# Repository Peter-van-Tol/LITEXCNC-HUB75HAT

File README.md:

# HUB75HAT

A PCB that turns the Colorlight 5A-75B into an easy to use CNC controller for cheap.

This project ist based on:
- [cyber-murmel/chubby-hat](https://github.com/cyber-murmel/chubby-hat)
- [3k/chubby75](https://github.com/q3k/chubby75/tree/master/5a-75b])

The [HUB75HAT](src/HUB75HAT) is 5A-75B motherboard host for a Raspberry Pi CPU. The HUB75HAT connects to the RPI’s GPIO interface and uses SPI for FPGA communication. Three 26 pin header connectors with standard parallel port pinouts and 5V tolerant I/O are provided for compatibility with most parallel port interfaced motion control / CNC breakout cards / multi axis step motor drives.

In addition to the parallel expansion ports, the HUB75HAT provides two RS-485 interfaces for I/O communication to other RS-485 applications, such as the Huanyang VFD series. These RS-485 are directly taken from the RPI’s header (UART0/1 and UART5).

The firmware is flashed onto the 5A-75B by using the RPI’s GPIO pins. There is no need for external programmers.

The motherboard can also be used _without_ the RPI, by using the standard ethernet communication of the 5A-75B. In this case one would loose the ability to use the RS-485 interfaces and an external tool will be required to flash new firmware.

## Breakout boards (BOB)
Breakout boards are available for the HUB75HAT. These BOBs are designed to add functionality to the HUB75HAT by
extending the GPIO from the 3 26 pin header connectors with drivers, receivers, opto-couplers, etc. Currently the
following BOBs are available:
- [BOB4AXIS](src/BOB4AXIS): Supports driving of 4 axis with differential output. Has inputs for the ALARM of the stepper
  drivers for each axis. Also has optocouplers for homing switches. The homing switches can be either NPN or PNP (selectable
  per axis). Adding this BOB would be enough to run a small 3 axis CNC machine with 1 slave axis.
- [BOB4ENCODER](src/BOB4ENCODER): Supports up to 4 encoders with index (5V only). Unused inputs can be used for generic
  IO. This board also has two connections for SERIAL boards, to further expand GPIO for your machine.

## Serial boards (SERIAL)
These boards are still under development. Goal is to extend GPIO with SPI expanders.

## Releases
The table below gives for each board the current status and the latest release. 

| board               | latest release                            |
|---------------------|-------------------------------------------|
| HUB75HAT            | [v1.2](src/HUB75HAT/releases/v1.2/)       |
| HC245T_BYPASS       | [v1.0](src/HC245T_BYPASS//releases/v1.0/) |
| BOB4AXIS            | [v1.1](src/BOB4AXIS/releases/v1.1/)       |
| BOB4ENCODER         | [v1.0](src/BOB4ENCODER/releases/v1.0/)    |

In each release folder you'll find a production folder with:
- a .zip-file which can be uploaded to your favorite PCB manufacturer
- a BOM;
- a position file for assembly (only verified for HUB75HAT, the rest is hand-soldered)

## KiCad Version
The following version of KiCad has been used to design the boards:
```
Application: KiCad x64 on x64
Version: 7.0.7, release build
Libraries:
    wxWidgets 3.2.2
    FreeType 2.12.1
    HarfBuzz 6.0.0
    FontConfig 2.14.1
    libcurl/7.88.1-DEV Schannel zlib/1.2.13

Platform: Windows 10 (build 19044), 64-bit edition, 64 bit, Little endian, wxMSW

Build Info:
    Date: Aug 19 2023 13:12:00
    wxWidgets: 3.2.2 (wchar_t,wx containers)
    Boost: 1.81.0
    OCC: 7.7.1
    Curl: 7.88.1-DEV
    ngspice: 40
    Compiler: Visual C++ 1936 without C++ ABI

Build settings:
    KICAD_SPICE=ON
```

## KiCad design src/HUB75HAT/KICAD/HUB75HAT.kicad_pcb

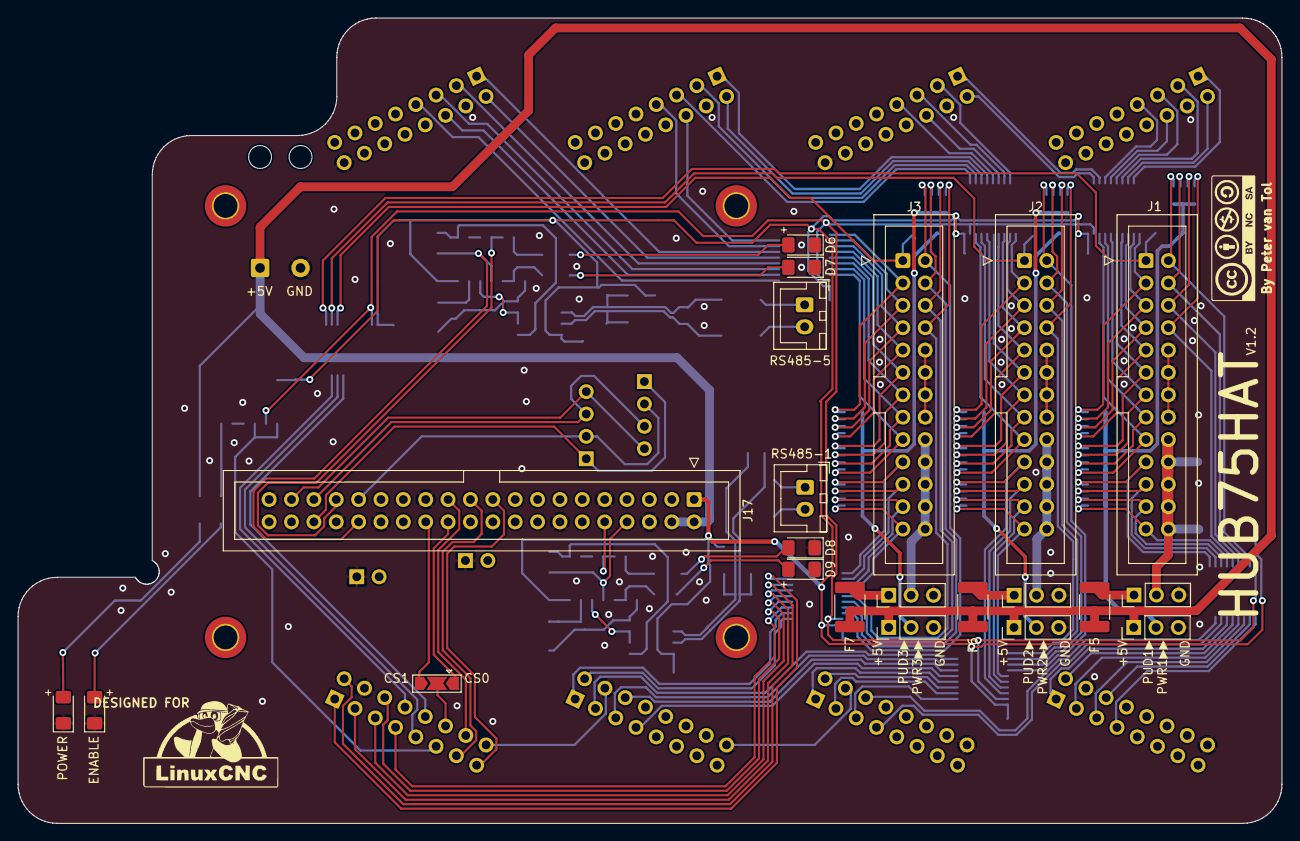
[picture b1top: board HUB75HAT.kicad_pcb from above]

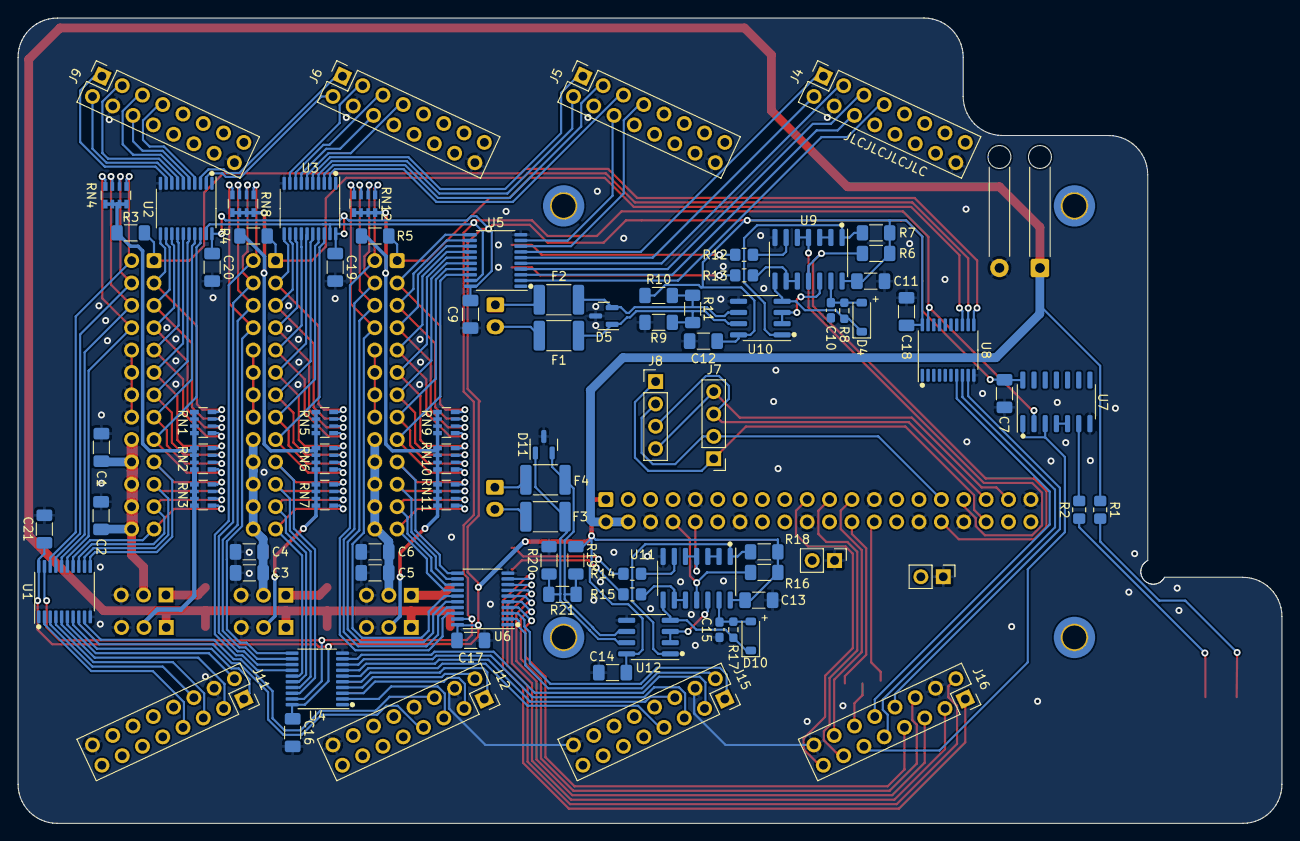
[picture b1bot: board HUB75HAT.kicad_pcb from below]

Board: 2 copper layers, 143.5 x 91.4 mm, 108 parts (86 on the bottom side), 160 nets.

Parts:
C1, C2, C3, C4, C5, C6, C7, C9, C11, C13, C16, C17, C18, C19, C20, C21: 100nF; C_1206_3216Metric_Pad1.33x1.80mm_HandSolder
C10, C15: 33pF; C_0603_1608Metric_Pad1.08x0.95mm_HandSolder
C12, C14: 0.1uF; C_1206_3216Metric_Pad1.33x1.80mm_HandSolder
D1, D2, D6, D7, D8, D9: LED; LED_1206_3216Metric_Pad1.42x1.75mm_HandSolder
D4, D10: 1N4148W; D_SOD-123
D5, D11: SM712_SOT23; SOT-23
F1, F2, F3, F4, F5, F6, F7: 108L; Fuse_1812_4532Metric_Pad1.30x3.40mm_HandSolder
J1, J2, J3: Conn_02x13_Odd_Even; IDC-Header_2x13_P2.54mm_Vertical
J4, J5, J6, J9, J11, J12, J15, J16: HUB75; PinSocket_2x08_P2.54mm_Vertical
J7: v7.0; PinHeader_1x04_P2.54mm_Vertical
J8: v8.0; PinHeader_1x04_P2.54mm_Vertical
J10: Conn_01x02; SolderWire-0.5sqmm_1x02_P4.6mm_D0.9mm_OD2.1mm_Relief
J13: V7.0; PinHeader_1x02_P2.54mm_Vertical
J14: V8.0; PinHeader_1x02_P2.54mm_Vertical
J17: Conn_02x20_Odd_Even; IDC-Header_2x20_P2.54mm_Vertical
JP1, JP2, JP3, JP4, JP5, JP6: Jumper_3_Open; PinHeader_1x03_P2.54mm_Vertical
JP7: SolderJumper_3_Open; SolderJumper-3_P2.0mm_Open_TrianglePad1.0x1.5mm
R1: 300; R_0805_2012Metric_Pad1.20x1.40mm_HandSolder
R2, R12, R13, R14, R15: 150; R_0805_2012Metric_Pad1.20x1.40mm_HandSolder
R3, R4, R5: R; R_1206_3216Metric_Pad1.30x1.75mm_HandSolder
R6, R16: 4.7k; R_1206_3216Metric_Pad1.30x1.75mm_HandSolder
R7, R9, R10, R18, R19, R20: 4.7K; R_1206_3216Metric_Pad1.30x1.75mm_HandSolder
R8, R17: 56k; R_0603_1608Metric_Pad0.98x0.95mm_HandSolder
R11, R21: 120; R_1206_3216Metric_Pad1.30x1.75mm_HandSolder
RN1, RN2, RN3, RN4, RN5, RN6, RN7, RN8, RN9, RN10, RN11, RN12: CN1J4KTTD1002F; R_Array_Convex_4x0603_handsolder
RS485-1, RS485-5: Conn_01x02_Pin; JST_XH_B2B-XH-A_1x02_P2.50mm_Vertical
U1, U2, U3, U4, U5, U6, U8: 74CB3T3245; TSSOP-20_4.4x6.5mm_P0.65mm
U7, U9, U11: 74HC04; SOIC-14_3.9x8.7mm_P1.27mm
U10, U12: MAX3485; SOIC-8_3.9x4.9mm_P1.27mm

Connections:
+3.3V: C7.1, C9.1, C11.1, C12.1, C13.1, C14.1, C16.1, C17.1, C18.1, C19.1, C20.1, C21.1, J17.1, R6.1, R7.1, R10.1, R16.1, R18.1, R19.1, U1.20 (VCC), U2.20 (VCC), U3.20 (VCC), U4.20 (VCC), U5.20 (VCC), U6.20 (VCC), U7.14 (VCC), U8.20 (VCC), U9.14 (VCC), U10.8 (VCC), U11.14 (VCC), U12.8 (VCC)
+5V: F5.1, F6.1, F7.1, J10.1, J17.2, J17.4, JP4.1 (A), JP5.1 (A), JP6.1 (A), R1.1
/JTAG.TCK: J7.1, J8.1, J17.36
/JTAG.TDI: J7.3, J8.3, J17.35
/JTAG.TDO: J7.4, J8.4, J17.37
/JTAG.TMS: J7.2, J8.2, J17.31
ENA: U1.19 (CE), U2.19 (CE), U3.19 (CE), U4.19 (CE), U5.19 (CE), U6.19 (CE), U7.2, U8.19 (CE)
ENA-LED: R2.1, U7.6
ENA_IN: J16.11, U7.1, U7.3
GND: C1.2, C2.2, C3.2, C4.2, C5.2, C6.2, C7.2, C9.2, C10.2, C11.2, C12.2, C13.2, C14.2, C15.2, C16.2, C17.2, C18.2, C19.2, C20.2, C21.2, D1.1 (K), D2.1 (K), D5.3 (common), D6.1 (K), D7.1 (K), D8.1 (K), D9.1 (K), D11.3 (common), J1.10, J1.12, J1.14, J1.16, J2.10, J2.12, J2.14, J2.16, J3.10, J3.12, J3.14, J3.16, J4.4, J4.16, J5.4, J5.16, J6.4, J6.16, J9.4, J9.16, J10.2, J11.4, J11.16, J12.4, J12.16, J13.1, J14.1, J15.4, J15.16, J16.4, J16.16, J17.6, J17.9, J17.14, J17.20, J17.25, J17.30, J17.34, J17.39, JP1.3 (B), JP2.3 (B), JP3.3 (B), JP4.3 (B), JP5.3 (B), JP6.3 (B), R9.2, R20.2, U1.10 (GND), U2.10 (GND), U3.10 (GND), U4.10 (GND), U5.10 (GND), U6.10 (GND), U7.7 (GND), U8.10 (GND), U9.7 (GND), U10.5 (GND), U11.7 (GND), U12.5 (GND)
J1:0: J11.1, U1.7 (A5)
J1:1: J11.2, U1.6 (A4)
J1:2: J11.3, U1.5 (A3)
J1:4: J11.5, U1.4 (A2)
J1:5: J11.6, U1.3 (A1)
J1:6: J11.7, U1.2 (A0)
J2:0: J12.1, U4.5 (A3)
J2:1: J12.2, U4.4 (A2)
J2:2: J12.3, U4.3 (A1)
J2:4: J12.5, U4.2 (A0)
J2:5: J12.6, U1.9 (A7)
J2:6: J12.7, U1.8 (A6)
J3:0: J15.1, U6.3 (A1)
J3:1: J15.2, U6.2 (A0)
J3:2: J15.3, U4.9 (A7)
J3:4: J15.5, U4.8 (A6)
J3:5: J15.6, U4.7 (A5)
J3:6: J15.7, U4.6 (A4)
J4:0: J16.1, U6.9 (A7)
J4:1: J16.2, U6.8 (A6)
J4:2: J16.3, U6.7 (A5)
J4:4: J16.5, U6.6 (A4)
J4:5: J16.6, U6.5 (A3)
J4:6: J16.7, U6.4 (A2)
J4:7: J16.8, U8.9 (A7)
J4:8: J16.9, U8.8 (A6)
J4:9: J16.10, U8.7 (A5)
J5:0: J4.1, U5.7 (A5)
J5:1: J4.2, U5.6 (A4)
J5:2: J4.3, U5.5 (A3)
J5:4: J4.5, U5.4 (A2)
J5:5: J4.6, U5.3 (A1)
J5:6: J4.7, U5.2 (A0)
J6:0: J5.1, U3.5 (A3)
J6:1: J5.2, U3.4 (A2)
J6:2: J5.3, U3.3 (A1)
J6:4: J5.5, U3.2 (A0)
J6:5: J5.6, U5.9 (A7)
J6:6: J5.7, U5.8 (A6)
J7:0: J6.1, U2.3 (A1)
J7:1: J6.2, U2.2 (A0)
J7:2: J6.3, U3.9 (A7)
J7:4: J6.5, U3.8 (A6)
J7:5: J6.6, U3.7 (A5)
J7:6: J6.7, U3.6 (A4)
J8:0: J9.1, U2.9 (A7)
J8:1: J9.2, U2.8 (A6)
J8:2: J9.3, U2.7 (A5)
J8:4: J9.5, U2.6 (A4)
J8:5: J9.6, U2.5 (A3)
J8:6: J9.7, U2.4 (A2)
unnamed: D1.2 (A), R1.2
unnamed: D2.2 (A), R2.2
unnamed: C10.1, D4.2 (A), R8.2, U9.13
unnamed: D4.1 (K), R8.1, U9.8, U10.4 (DI)
unnamed: D5.1 (A1), F1.1, R9.1, R11.1, U10.7 (B)
unnamed: D5.2 (A2), F2.2, R10.2, R11.2, U10.6 (A)
unnamed: D6.2 (A), R12.2
unnamed: D7.2 (A), R13.2
unnamed: D8.2 (A), R14.2
unnamed: D9.2 (A), R15.2
unnamed: C15.1, D10.2 (A), R17.2, U11.13
unnamed: D10.1 (K), R17.1, U11.8, U12.4 (DI)
unnamed: D11.1 (A1), F3.1, R20.1, R21.1, U12.7 (B)
unnamed: D11.2 (A2), F4.2, R19.2, R21.2, U12.6 (A)
unnamed: F2.1, RS485-5.1
unnamed: F1.2, RS485-5.2
unnamed: F4.1, RS485-1.1
unnamed: F3.2, RS485-1.2
unnamed: F5.2, JP1.1 (A)
unnamed: F6.2, JP2.1 (A)
unnamed: F7.2, JP3.1 (A)
unnamed: JP4.2 (C), R3.2, RN1.1 (R1.1), RN1.2 (R2.1), RN1.3 (R3.1), RN1.4 (R4.1), RN2.1 (R1.1), RN2.2 (R2.1), RN2.3 (R3.1), RN2.4 (R4.1), RN3.1 (R1.1), RN3.2 (R2.1), RN3.3 (R3.1), RN3.4 (R4.1), RN4.1 (R1.1), RN4.2 (R2.1), RN4.3 (R3.1), RN4.4 (R4.1)
unnamed: JP5.2 (C), R4.2, RN5.1 (R1.1), RN5.2 (R2.1), RN5.3 (R3.1), RN5.4 (R4.1), RN6.1 (R1.1), RN6.2 (R2.1), RN6.3 (R3.1), RN6.4 (R4.1), RN7.1 (R1.1), RN7.2 (R2.1), RN7.3 (R3.1), RN7.4 (R4.1), RN8.1 (R1.1), RN8.2 (R2.1), RN8.3 (R3.1), RN8.4 (R4.1)
unnamed: JP6.2 (C), R5.2, RN9.1 (R1.1), RN9.2 (R2.1), RN9.3 (R3.1), RN9.4 (R4.1), RN10.1 (R1.1), RN10.2 (R2.1), RN10.3 (R3.1), RN10.4 (R4.1), RN11.1 (R1.1), RN11.2 (R2.1), RN11.3 (R3.1), RN11.4 (R4.1), RN12.1 (R1.1), RN12.2 (R2.1), RN12.3 (R3.1), RN12.4 (R4.1)
unnamed: R12.1, U9.6
unnamed: R13.1, U9.9, U9.10
unnamed: R14.1, U11.6
unnamed: R15.1, U11.9, U11.10
unnamed: U7.4, U7.5
unnamed: U9.2, U9.3
unnamed: U9.12, U10.2 (~RE), U10.3 (DE)
unnamed: R7.2, U9.1, U10.1 (RO)
unnamed: U11.2, U11.3
unnamed: U11.12, U12.2 (~RE), U12.3 (DE)
unnamed: R18.2, U11.1, U12.1 (RO)
PORTA1: J1.1, R3.1, U8.11 (B7)
PORTA2: J1.3, RN1.8 (R1.2), U2.11 (B7)
PORTA3: J1.5, RN1.7 (R2.2), U2.12 (B6)
PORTA4: J1.7, RN1.6 (R3.2), U2.13 (B5)
PORTA5: J1.9, RN1.5 (R4.2), U2.14 (B4)
PORTA6: J1.11, RN2.8 (R1.2), U2.15 (B3)
PORTA7: J1.13, RN2.7 (R2.2), U2.16 (B2)
PORTA8: J1.15, RN2.6 (R3.2), U2.17 (B1)
PORTA9: J1.17, RN2.5 (R4.2), U2.18 (B0)
PORTA10: J1.19, RN3.8 (R1.2), U1.11 (B7)
PORTA11: J1.21, RN3.7 (R2.2), U1.12 (B6)
PORTA12: J1.23, RN3.6 (R3.2), U1.13 (B5)
PORTA13: J1.25, RN3.5 (R4.2), U1.14 (B4)
PORTA14: J1.2, RN4.5 (R4.2), U1.18 (B0)
PORTA15: J1.4, RN4.6 (R3.2), U1.17 (B1)
PORTA16: J1.6, RN4.7 (R2.2), U1.16 (B2)
PORTA17: J1.8, RN4.8 (R1.2), U1.15 (B3)
PORTB1: J2.1, R4.1, U8.12 (B6)
PORTB2: J2.3, RN5.8 (R1.2), U3.11 (B7)
PORTB3: J2.5, RN5.7 (R2.2), U3.12 (B6)
PORTB4: J2.7, RN5.6 (R3.2), U3.13 (B5)
PORTB5: J2.9, RN5.5 (R4.2), U3.14 (B4)
PORTB6: J2.11, RN6.8 (R1.2), U3.15 (B3)
PORTB7: J2.13, RN6.7 (R2.2), U3.16 (B2)
PORTB8: J2.15, RN6.6 (R3.2), U3.17 (B1)
PORTB9: J2.17, RN6.5 (R4.2), U3.18 (B0)
PORTB10: J2.19, RN7.8 (R1.2), U4.18 (B0)
PORTB11: J2.21, RN7.7 (R2.2), U4.17 (B1)
PORTB12: J2.23, RN7.6 (R3.2), U4.16 (B2)
PORTB13: J2.25, RN7.5 (R4.2), U4.15 (B3)
PORTB14: J2.2, RN8.5 (R4.2), U4.14 (B4)
PORTB15: J2.4, RN8.6 (R3.2), U4.13 (B5)
PORTB16: J2.6, RN8.7 (R2.2), U4.12 (B6)
PORTB17: J2.8, RN8.8 (R1.2), U4.11 (B7)
PORTC1: J3.1, R5.1, U8.13 (B5)
PORTC2: J3.3, RN9.8 (R1.2), U5.11 (B7)
PORTC3: J3.5, RN9.7 (R2.2), U5.12 (B6)
PORTC4: J3.7, RN9.6 (R3.2), U5.13 (B5)
PORTC5: J3.9, RN9.5 (R4.2), U5.14 (B4)
PORTC6: J3.11, RN10.8 (R1.2), U5.15 (B3)
PORTC7: J3.13, RN10.7 (R2.2), U5.16 (B2)
PORTC8: J3.15, RN10.6 (R3.2), U5.17 (B1)
PORTC9: J3.17, RN10.5 (R4.2), U5.18 (B0)
PORTC10: J3.19, RN11.8 (R1.2), U6.11 (B7)
PORTC11: J3.21, RN11.7 (R2.2), U6.12 (B6)
PORTC12: J3.23, RN11.6 (R3.2), U6.13 (B5)
PORTC13: J3.25, RN11.5 (R4.2), U6.14 (B4)
PORTC14: J3.2, RN12.5 (R4.2), U6.18 (B0)
PORTC15: J3.4, RN12.6 (R3.2), U6.17 (B1)
PORTC16: J3.6, RN12.7 (R2.2), U6.16 (B2)
PORTC17: J3.8, RN12.8 (R1.2), U6.15 (B3)
POWOPA: C1.1, C2.1, J1.18, J1.20, J1.22, J1.24, J1.26, JP1.2 (C)
POWOPB: C3.1, C4.1, J2.18, J2.20, J2.22, J2.24, J2.26, JP2.2 (C)
POWOPC: C5.1, C6.1, J3.18, J3.20, J3.22, J3.24, J3.26, JP3.2 (C)
RXD1: J17.10, U11.4, U11.5
RXD5: J17.33, U9.4, U9.5
SPI_CE0: J17.24, JP7.1 (A)
SPI_CE1: J17.26, JP7.3 (B)
SPI_CLCK: J16.14, J17.23
SPI_CS: J16.12, JP7.2 (C)
SPI_MISO: J16.13, J17.21
SPI_MOSI: J16.15, J17.19
TXD1: J17.8, R16.2, U11.11
TXD5: J17.32, R6.2, U9.11

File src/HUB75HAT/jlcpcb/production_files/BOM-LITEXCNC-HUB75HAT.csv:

Comment,Designator,Footprint,LCSC
74CB3T3245,"U1,U2,U3,U4,U5,U6,U8",TSSOP-20_4.4x6.5mm_P0.65mm,C15298
33pF,"C10,C15",C_0603_1608Metric_Pad1.08x0.95mm_HandSolder,C1663
150,"R12,R13,R14,R15,R2",R_0805_2012Metric_Pad1.20x1.40mm_HandSolder,C17471
300,R1,R_0805_2012Metric_Pad1.20x1.40mm_HandSolder,C17617
R,"R3,R4,R5",R_1206_3216Metric_Pad1.30x1.75mm_HandSolder,C17902
120,"R11,R21",R_1206_3216Metric_Pad1.30x1.75mm_HandSolder,C17909
4.7K,"R10,R16,R18,R19,R20,R6,R7,R9",R_1206_3216Metric_Pad1.30x1.75mm_HandSolder,C17936
56k,"R17,R8",R_0603_1608Metric_Pad0.98x0.95mm_HandSolder,C23206
100nF,"C1,C11,C12,C13,C14,C16,C17,C18,C19,C2,C20,C21,C3,C4,C5,C6,C7,C9",C_1206_3216Metric_Pad1.33x1.80mm_HandSolder,C24497
SM712_SOT23,"D11,D5",SOT-23,C2687124
CN1J4KTTD1002F,"RN1,RN10,RN11,RN12,RN2,RN3,RN4,RN5,RN6,RN7,RN8,RN9",R_Array_Convex_4x0603_handsolder,C29718
108L,"F1,F2,F3,F4,F5,F6,F7",Fuse_1812_4532Metric_Pad1.30x3.40mm_HandSolder,C782760
MAX3485,"U10,U12",SOIC-8_3.9x4.9mm_P1.27mm,C8963
LED,D1,LED_1206_3216Metric_Pad1.42x1.75mm_HandSolder,
LED,D2,LED_1206_3216Metric_Pad1.42x1.75mm_HandSolder,
74HC04,U9,SOIC-14_3.9x8.7mm_P1.27mm,
74HC04,U11,SOIC-14_3.9x8.7mm_P1.27mm,
1N4148W,D4,D_SOD-123,
1N4148W,D10,D_SOD-123,
LED,D9,LED_1206_3216Metric_Pad1.42x1.75mm_HandSolder,
LED,D6,LED_1206_3216Metric_Pad1.42x1.75mm_HandSolder,
LED,D7,LED_1206_3216Metric_Pad1.42x1.75mm_HandSolder,
LED,D8,LED_1206_3216Metric_Pad1.42x1.75mm_HandSolder,
74HC04,U7,SOIC-14_3.9x8.7mm_P1.27mm,

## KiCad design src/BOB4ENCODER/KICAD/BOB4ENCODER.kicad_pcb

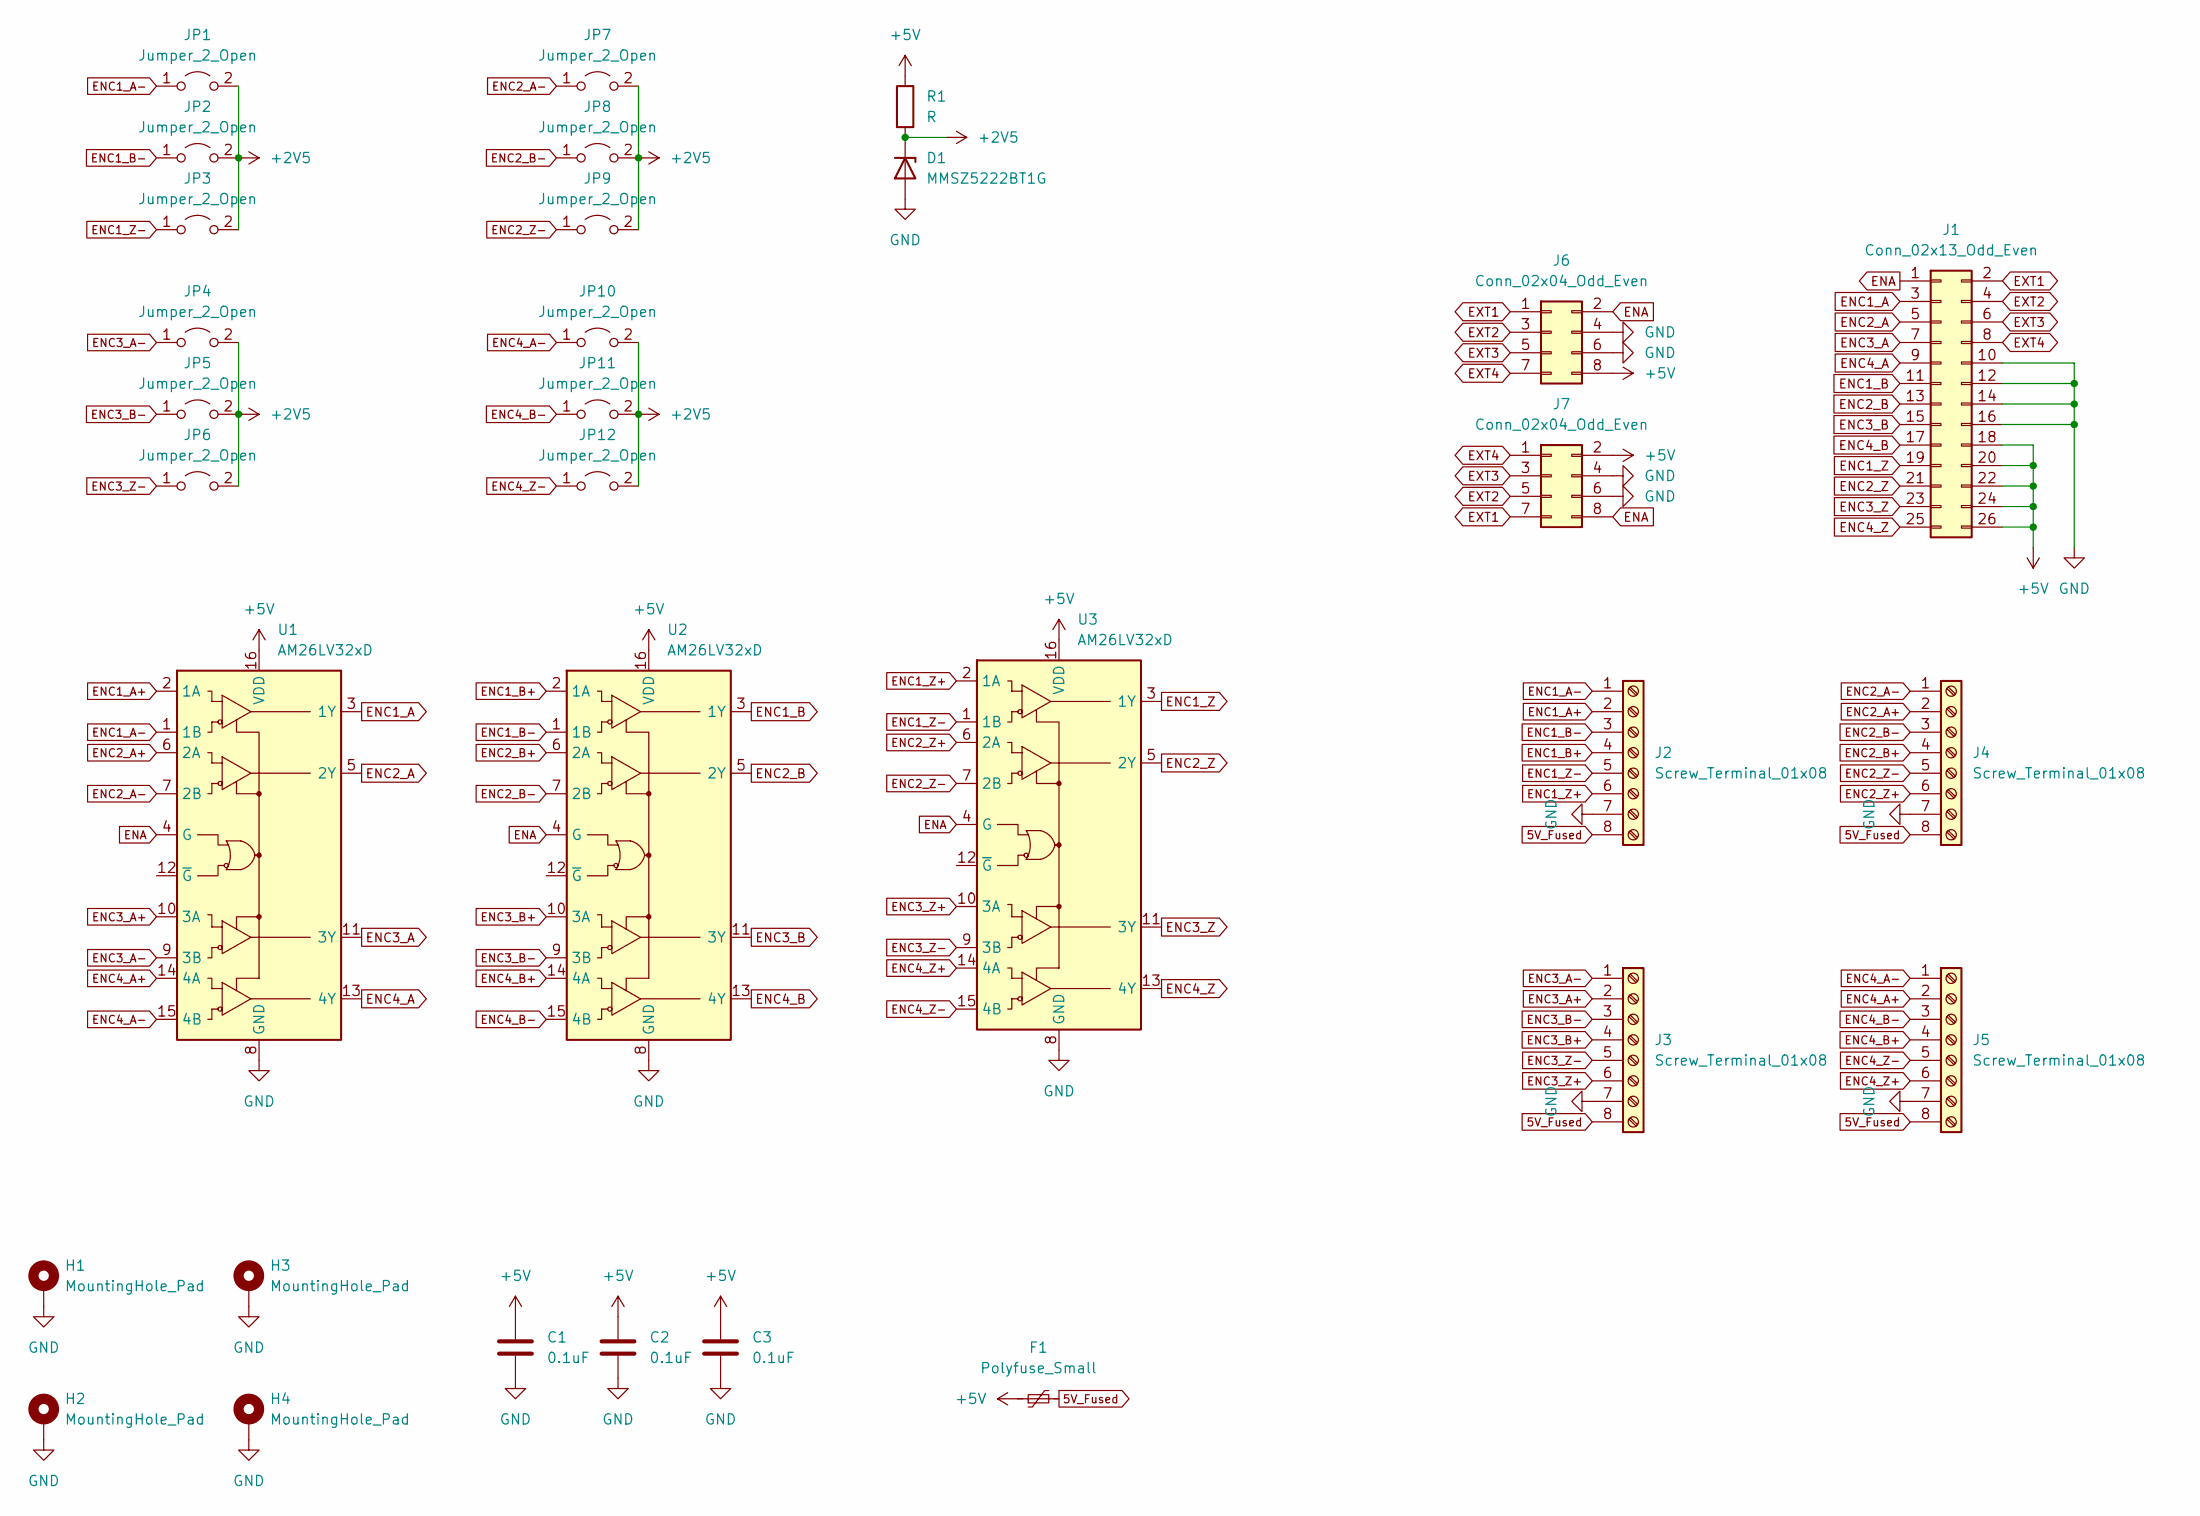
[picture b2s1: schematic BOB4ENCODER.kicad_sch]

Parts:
C1, C2, C3: 0.1uF; C_1206_3216Metric_Pad1.33x1.80mm_HandSolder
D1: MMSZ5222BT1G; D_SOD-123
F1: Polyfuse_Small; R_1812_4532Metric_Pad1.30x3.40mm_HandSolder
H1, H2, H3, H4: MountingHole_Pad; MountingHole_3.2mm_M3_Pad_Via
J1: Conn_02x13_Odd_Even; IDC-Header_2x13_P2.54mm_Vertical
J2, J3, J4, J5: Screw_Terminal_01x08; CONN-TH_8P-P5.08_KF142V-5.08-8P
J6, J7: Conn_02x04_Odd_Even; PinSocket_2x04_P1.27mm_Horizontal
JP1, JP2, JP3, JP4, JP5, JP6, JP7, JP8, JP9, JP10, JP11, JP12: Jumper_2_Open; PinHeader_1x02_P2.54mm_Vertical
R1: R; R_1206_3216Metric_Pad1.30x1.75mm_HandSolder
U1, U2, U3: AM26LV32xD; SOIC-16_3.9x9.9mm_P1.27mm

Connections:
5V_Fused: F1.2, J2.8, J3.8, J4.8, J5.8
+2V5: D1.1 (K), JP1.2 (B), JP2.2 (B), JP3.2 (B), JP4.2 (B), JP5.2 (B), JP6.2 (B), JP7.2 (B), JP8.2 (B), JP9.2 (B), JP10.2 (B), JP11.2 (B), JP12.2 (B), R1.2
+5V: C1.1, C2.1, C3.1, F1.1, J1.18, J1.20, J1.22, J1.24, J1.26, J6.8, J7.2, R1.1, U1.16 (VDD), U2.16 (VDD), U3.16 (VDD)
ENA: J1.1, J6.2, J7.8, U1.4 (G), U2.4 (G), U3.4 (G)
ENC1_A: J1.3, U1.3 (1Y)
ENC1_A+: J2.2, U1.2 (1A)
ENC1_A-: J2.1, JP1.1 (A), U1.1 (1B)
ENC1_B: J1.11, U2.3 (1Y)
ENC1_B+: J2.4, U2.2 (1A)
ENC1_B-: J2.3, JP2.1 (A), U2.1 (1B)
ENC1_Z: J1.19, U3.3 (1Y)
ENC1_Z+: J2.6, U3.2 (1A)
ENC1_Z-: J2.5, JP3.1 (A), U3.1 (1B)
ENC2_A: J1.5, U1.5 (2Y)
ENC2_A+: J4.2, U1.6 (2A)
ENC2_A-: J4.1, JP7.1 (A), U1.7 (2B)
ENC2_B: J1.13, U2.5 (2Y)
ENC2_B+: J4.4, U2.6 (2A)
ENC2_B-: J4.3, JP8.1 (A), U2.7 (2B)
ENC2_Z: J1.21, U3.5 (2Y)
ENC2_Z+: J4.6, U3.6 (2A)
ENC2_Z-: J4.5, JP9.1 (A), U3.7 (2B)
ENC3_A: J1.7, U1.11 (3Y)
ENC3_A+: J3.2, U1.10 (3A)
ENC3_A-: J3.1, JP4.1 (A), U1.9 (3B)
ENC3_B: J1.15, U2.11 (3Y)
ENC3_B+: J3.4, U2.10 (3A)
ENC3_B-: J3.3, JP5.1 (A), U2.9 (3B)
ENC3_Z: J1.23, U3.11 (3Y)
ENC3_Z+: J3.6, U3.10 (3A)
ENC3_Z-: J3.5, JP6.1 (A), U3.9 (3B)
ENC4_A: J1.9, U1.13 (4Y)
ENC4_A+: J5.2, U1.14 (4A)
ENC4_A-: J5.1, JP10.1 (A), U1.15 (4B)
ENC4_B: J1.17, U2.13 (4Y)
ENC4_B+: J5.4, U2.14 (4A)
ENC4_B-: J5.3, JP11.1 (A), U2.15 (4B)
ENC4_Z: J1.25, U3.13 (4Y)
ENC4_Z+: J5.6, U3.14 (4A)
ENC4_Z-: J5.5, JP12.1 (A), U3.15 (4B)
EXT1: J1.2, J6.1, J7.7
EXT2: J1.4, J6.3, J7.5
EXT3: J1.6, J6.5, J7.3
EXT4: J1.8, J6.7, J7.1
GND: C1.2, C2.2, C3.2, D1.2 (A), H1.1, H2.1, H3.1, H4.1, J1.10, J1.12, J1.14, J1.16, J2.7, J3.7, J4.7, J5.7, J6.4, J6.6, J7.4, J7.6, U1.8 (GND), U2.8 (GND), U3.8 (GND)

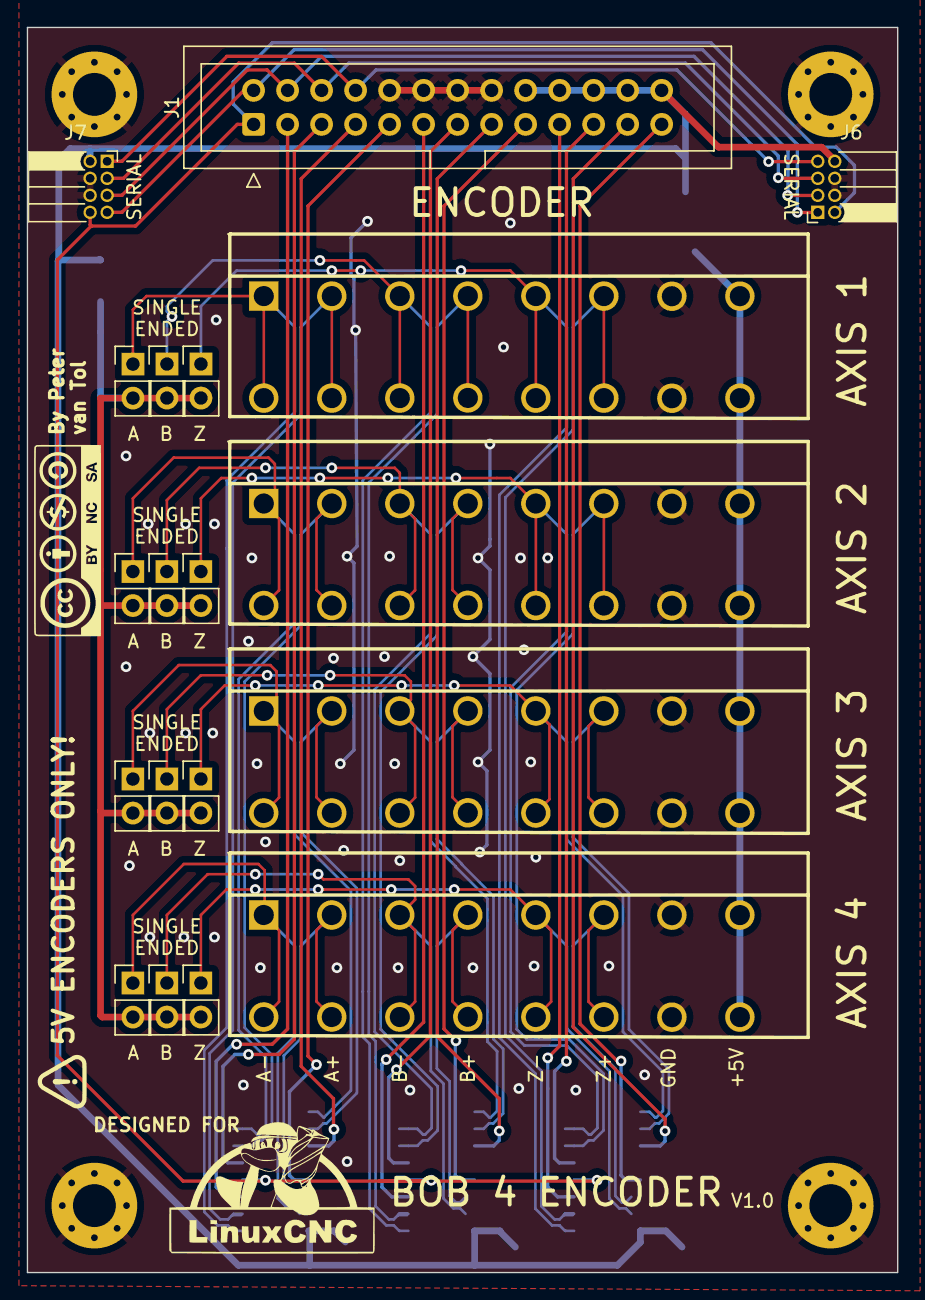
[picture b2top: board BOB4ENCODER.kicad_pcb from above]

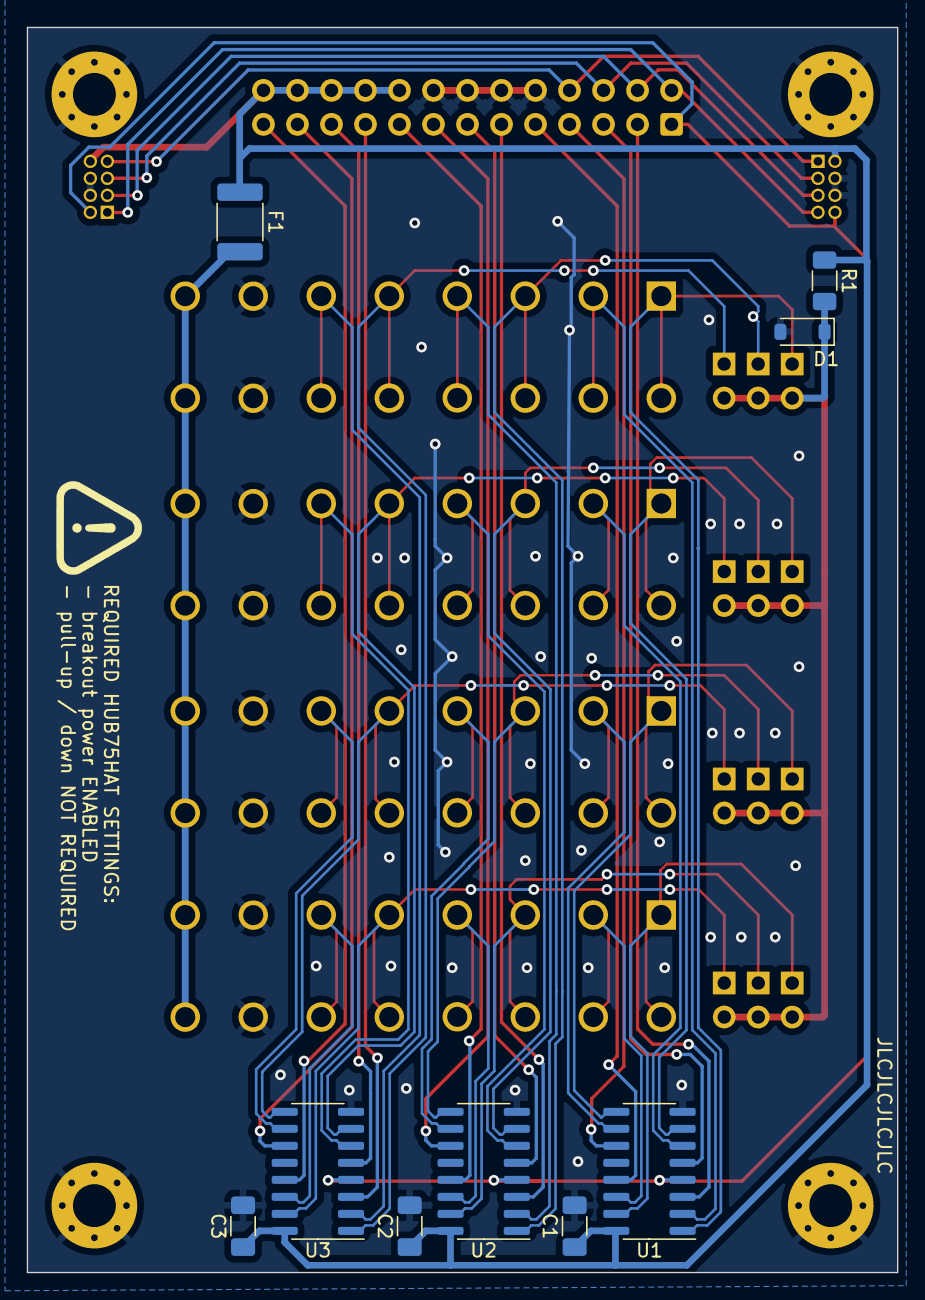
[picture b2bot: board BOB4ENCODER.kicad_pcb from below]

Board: 2 copper layers, 65.0 x 93.0 mm, 32 parts (9 on the bottom side), 45 nets.

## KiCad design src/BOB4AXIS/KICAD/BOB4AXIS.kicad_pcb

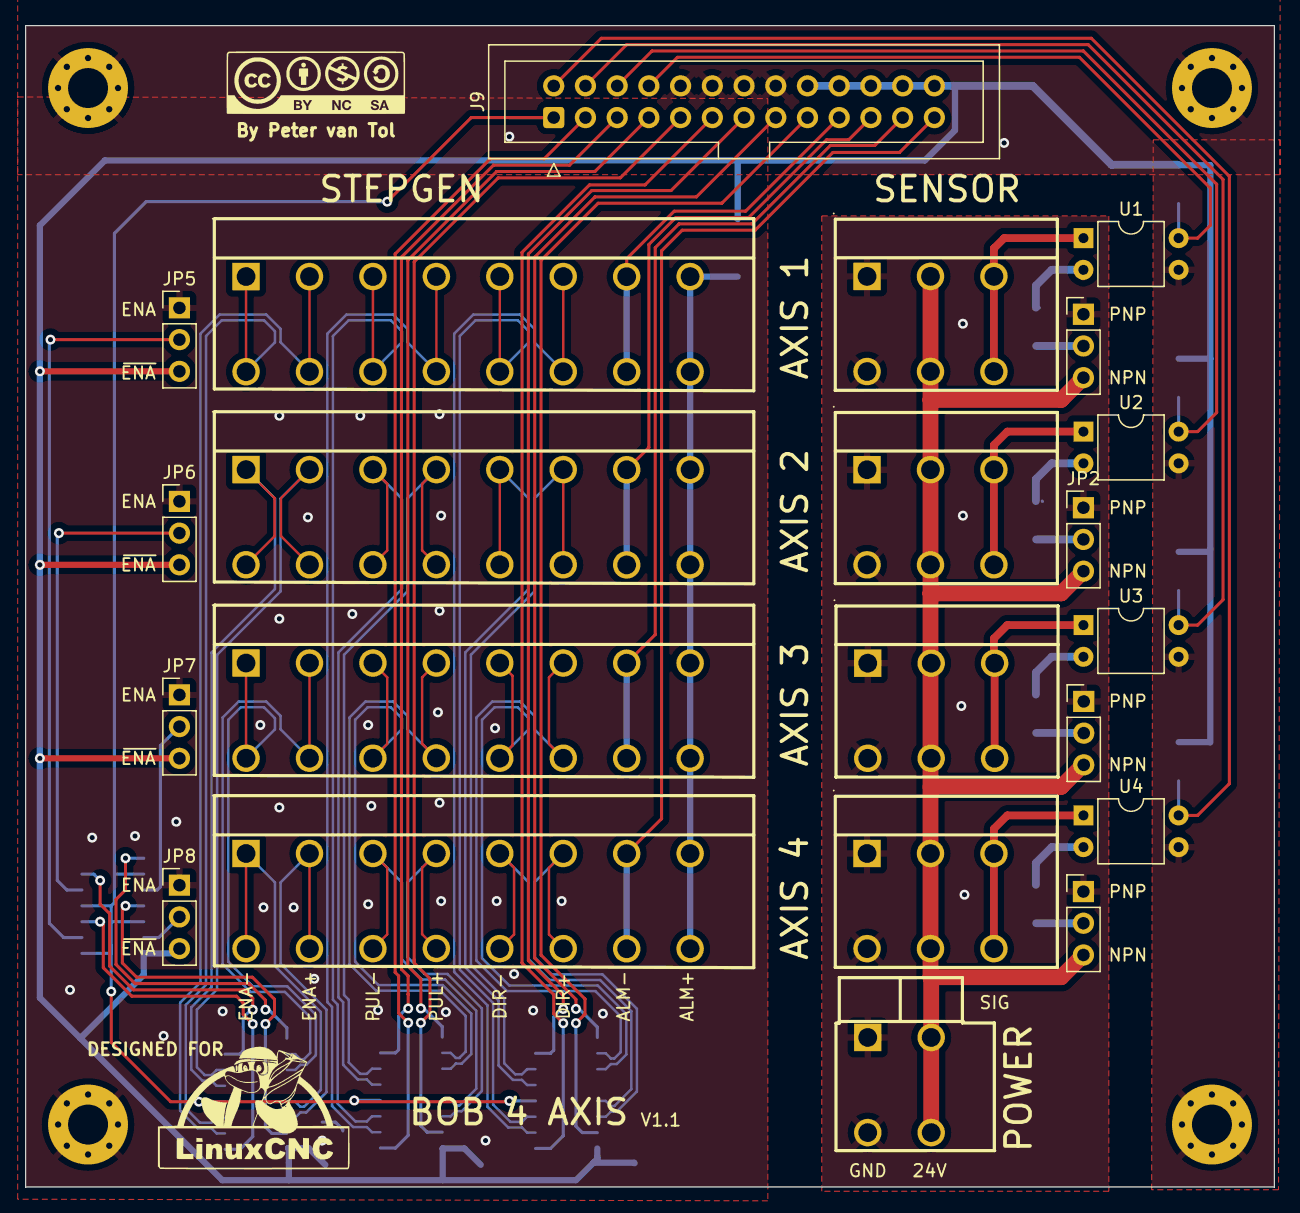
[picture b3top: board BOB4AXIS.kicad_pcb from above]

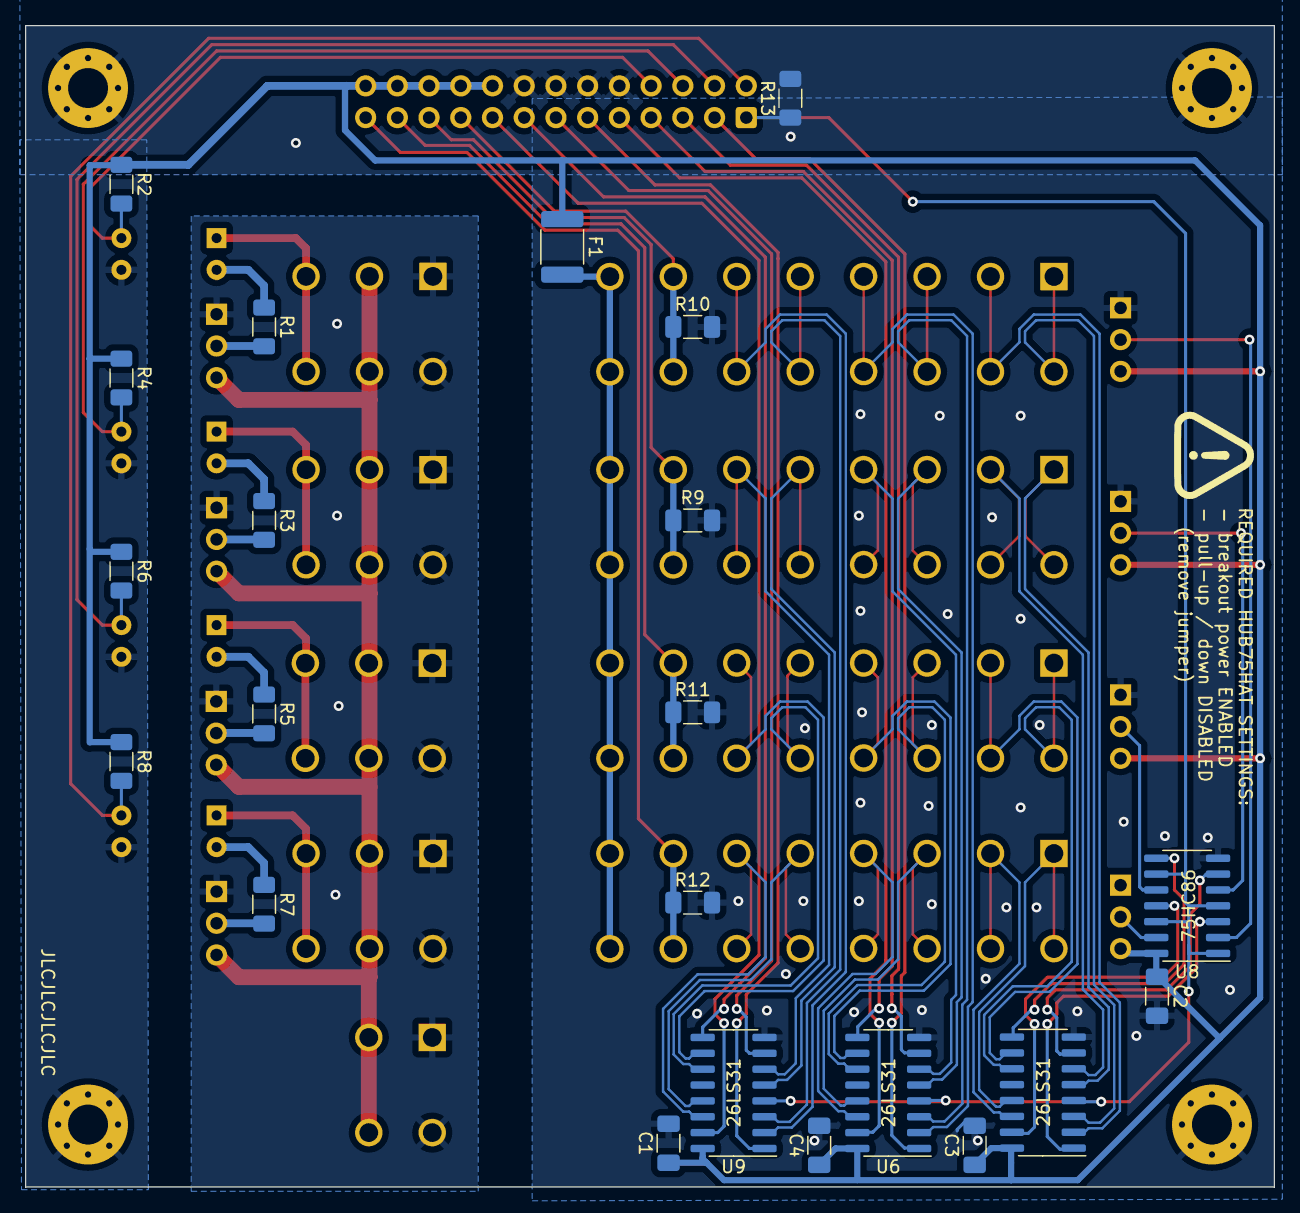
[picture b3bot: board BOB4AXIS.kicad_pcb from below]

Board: 2 copper layers, 100.0 x 93.0 mm, 48 parts (22 on the bottom side), 66 nets.

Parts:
C1, C2, C3, C4: 0.1uF; C_1206_3216Metric_Pad1.33x1.80mm_HandSolder
F1: Polyfuse_Small; R_1812_4532Metric_Pad1.30x3.40mm_HandSolder
H1, H2, H3, H4: MountingHole_Pad; MountingHole_3.2mm_M3_Pad_Via
J1, J2, J3, J4: Screw_Terminal_01x03; CONN-TH_3P-P5.08_KF142V-5.08-3P
J5, J6, J7, J8: Screw_Terminal_01x08; CONN-TH_8P-P5.08_KF142V-5.08-8P
J9: Conn_02x13_Odd_Even; IDC-Header_2x13_P2.54mm_Vertical
JP1, JP2, JP3, JP4, JP5, JP6, JP7, JP8: Jumper_3_Open; PinHeader_1x03_P2.54mm_Vertical
R1, R3, R5: 1k; R_1206_3216Metric_Pad1.30x1.75mm_HandSolder
R2, R4, R6, R8, R9, R10, R11, R12, R13: 10k; R_1206_3216Metric_Pad1.30x1.75mm_HandSolder
R7: R; R_1206_3216Metric_Pad1.30x1.75mm_HandSolder
U1, U2, U3, U4: LTV-814; DIP-4_W7.62mm
U5, U6, U9: AM26LS31CD; SOIC-16_3.9x9.9mm_P1.27mm
U7: KF142V-5_08-2P; CONN-TH_P5.08_KF142V-5.08-2P
U8: 74HC86; SOIC-14_3.9x8.7mm_P1.27mm

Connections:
5V_Fused: F1.2, J5.8, J6.8, J7.8, J8.8
+5V: C1.1, C2.1, C3.1, C4.1, F1.1, J9.18, J9.20, J9.22, J9.24, J9.26, JP5.3 (B), JP6.3 (B), JP7.3 (B), JP8.3 (B), R2.1, R4.1, R6.1, R8.1, U5.16 (VDD), U6.16 (VDD), U8.14 (VCC), U9.16 (VDD)
+24V: J1.2, J2.2, J3.2, J4.2, JP1.3 (B), JP2.3 (B), JP3.3 (B), JP4.3 (B), U7.1
ALARM1: J5.7, J9.19, R10.1
ALARM2: J6.7, J9.21, R9.1
ALARM3: J7.7, J9.23, R11.1
ALARM4: J8.7, J9.25, R12.1
DIR1: J9.11, U9.1 (1A)
DIR1+: J5.6, U9.2 (1Y)
DIR1-: J5.5, U9.3 (1Z)
DIR2: J9.13, U9.7 (2A)
DIR2+: J6.6, U9.6 (2Y)
DIR2-: J6.5, U9.5 (2Z)
DIR3: J9.15, U9.9 (3A)
DIR3+: J7.6, U9.10 (3Y)
DIR3-: J7.5, U9.11 (3Z)
DIR4: J9.17, U9.15 (4A)
DIR4+: J8.6, U9.14 (4Y)
DIR4-: J8.5, U9.13 (4Z)
ENA: J9.1, R13.1, U5.4 (G), U6.4 (G), U8.1, U8.4, U8.9, U8.12, U9.4 (G)
ENA1: U5.1 (1A), U8.3
ENA1+: J5.2, U5.2 (1Y)
ENA1-: J5.1, U5.3 (1Z)
ENA2: U5.7 (2A), U8.6
ENA2+: J6.2, U5.6 (2Y)
ENA2-: J6.1, U5.5 (2Z)
ENA3: U5.9 (3A), U8.8
ENA3+: J7.2, U5.10 (3Y)
ENA3-: J7.1, U5.11 (3Z)
ENA4: U5.15 (4A), U8.11
ENA4+: J8.2, U5.14 (4Y)
ENA4-: J8.1, U5.13 (4Z)
GND: C1.2, C2.2, C3.2, C4.2, H1.1, H2.1, H3.1, H4.1, J9.10, J9.12, J9.14, J9.16, JP5.1 (A), JP6.1 (A), JP7.1 (A), JP8.1 (A), R9.2, R10.2, R11.2, R12.2, R13.2, U1.3, U2.3, U3.3, U4.3, U5.8 (GND), U6.8 (GND), U8.7 (GND), U9.8 (GND)
GND1: J1.1, J2.1, J3.1, J4.1, JP1.1 (A), JP2.1 (A), JP3.1 (A), JP4.1 (A), U7.2
HOME1: J9.8, R2.2, U1.4
HOME2: J9.6, R4.2, U2.4
HOME3: J9.4, R6.2, U3.4
HOME4: J9.2, R8.2, U4.4
unnamed: J1.3, U1.1
unnamed: J2.3, U2.1
unnamed: J3.3, U3.1
unnamed: J4.3, U4.1
unnamed: JP1.2 (C), R1.2
unnamed: JP2.2 (C), R3.2
unnamed: JP3.2 (C), R5.2
unnamed: JP4.2 (C), R7.2
unnamed: JP5.2 (C), U8.2
unnamed: JP6.2 (C), U8.5
unnamed: JP7.2 (C), U8.10
unnamed: JP8.2 (C), U8.13
unnamed: R1.1, U1.2
unnamed: R3.1, U2.2
unnamed: R5.1, U3.2
unnamed: R7.1, U4.2
STEP1: J9.3, U6.1 (1A)
STEP1+: J5.4, U6.2 (1Y)
STEP1-: J5.3, U6.3 (1Z)
STEP2: J9.5, U6.7 (2A)
STEP2+: J6.4, U6.6 (2Y)
STEP2-: J6.3, U6.5 (2Z)
STEP3: J9.7, U6.9 (3A)
STEP3+: J7.4, U6.10 (3Y)
STEP3-: J7.3, U6.11 (3Z)
STEP4: J9.9, U6.15 (4A)
STEP4+: J8.4, U6.14 (4Y)
STEP4-: J8.3, U6.13 (4Z)

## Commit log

2023-09-18 Finished first versiom
2023-09-18 Initial commit documentation
2023-09-30 RPi configuration - initial commit
2023-09-30 Proto-type board finished
2023-09-30 Draft of modification to FPGA
2023-10-16 Prototype ordered
2023-10-25 Add symbols for parts from AliExpress
2023-10-25 Relative paths
2023-10-27 Decoupling capacitors
2023-10-27 Updated production files
2023-10-27 3D-model
2023-10-29 Small (non-functional) updates
2023-11-19 Iniital commit
2023-11-19 Version 1.1
2023-11-19 Fix missing imports
2023-11-19 Extended introduction
2023-11-19 Updated for v1.1
2023-11-19 Markup mistake
2023-11-19 Added power + pull-up
2023-11-19 Added Preparing 5A-75B
2023-11-19 Added UART, removed OpenOCD
2023-11-19 Updated labels
2023-11-19 Fix code-blocks
2023-11-19 Mask instead of disable
2024-01-09 Refactor the repo
2024-01-09 Fix links
2024-01-09 Added link to HUB75HAT
2024-01-09 Moving to new structure
2024-01-09 Remove lock files
2024-01-09 Fix typo
2024-01-11 Add pull-down resistor on ENA
2024-01-11 BOB4AXIS: release v1.0
2024-01-11 BOB4AXIS: release v1.1
2024-01-11 Remove old production files
2024-01-11 Move components away from src
2024-01-11 Update latest version
2024-01-11 BOB4ENCODER: release v1.0
2024-01-11 Move to images
2024-01-11 Version 1.1 produced
2024-01-11 HUB75HAT: release version 1.0
2024-01-11 HUB75HAT: release version 1.1
2024-01-11 Update with latest releases
2024-01-11 Rename production to releases
2024-01-11 Fix markup of table
2024-01-11 HC245T_BYPASS: Initial commit
2024-01-11 Add HC245T_BYPASS
2024-01-11 Corrected uart number
2024-01-13 Solved problem with J17 (GPIO header)
2024-01-13 Renamed / removing prefix LITEXCNC
2024-01-13 Release v1.2
2024-01-13 Update after save (rounding)
2024-01-13 Clearified text
